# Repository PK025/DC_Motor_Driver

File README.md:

# DC_Motor_Driver

Bidirectional DC motor driver, compatible with Arduino.

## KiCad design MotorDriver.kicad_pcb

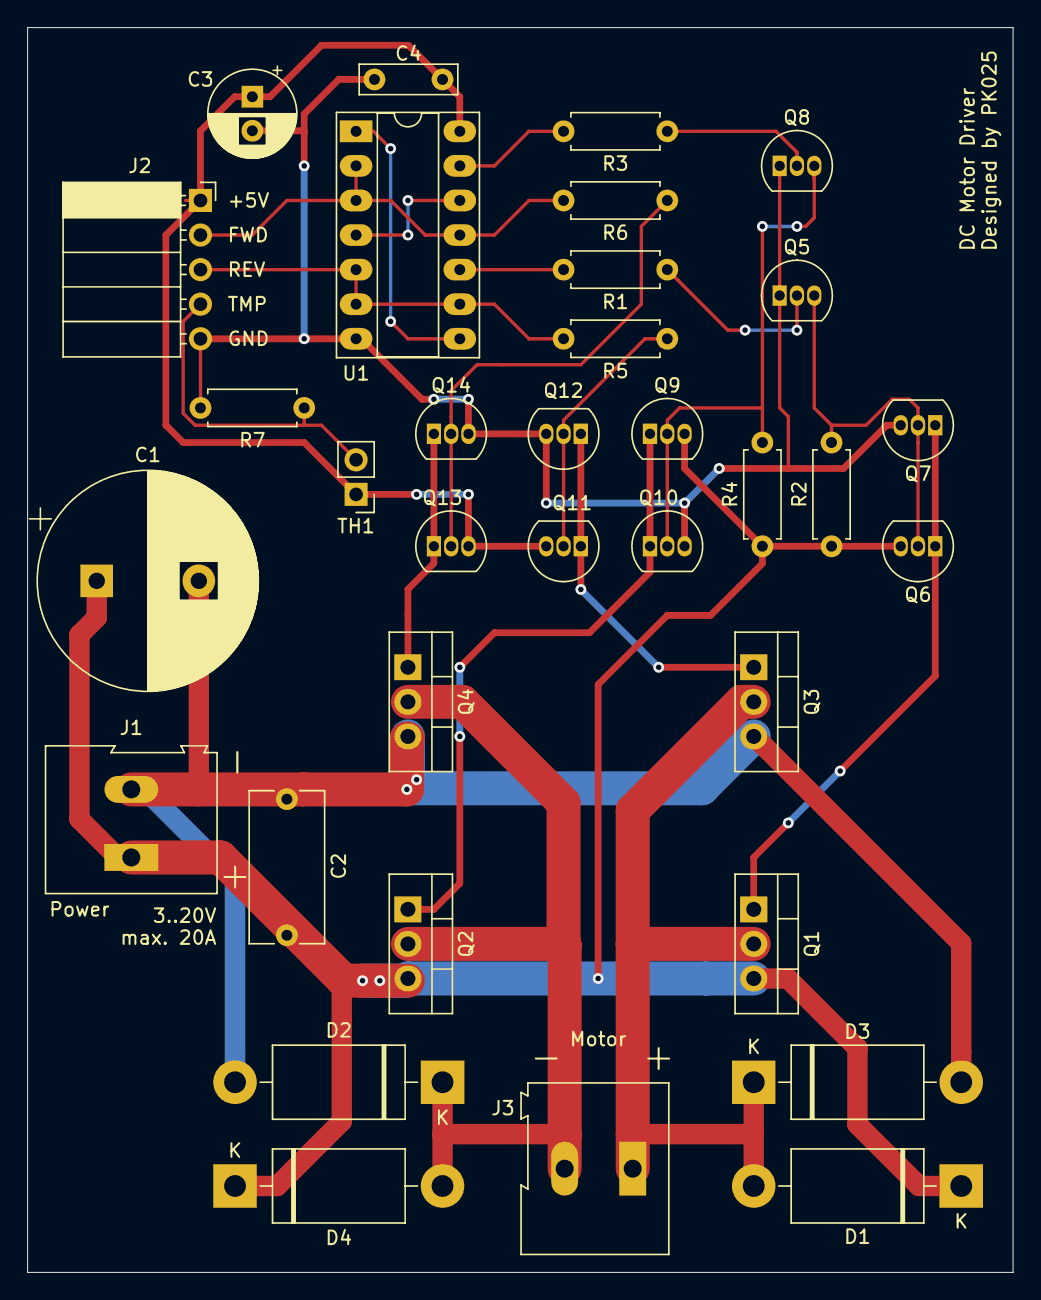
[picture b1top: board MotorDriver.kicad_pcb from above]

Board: 2 copper layers, 72.4 x 91.4 mm, 34 parts (0 on the bottom side), 23 nets.

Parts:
C1: 1000μF; CP_Radial_D16.0mm_P7.50mm
C2: 100nF; C_Rect_L11.0mm_W5.3mm_P10.00mm_MKT
C3: 47μF; CP_Radial_D6.3mm_P2.50mm
C4: 100nF; C_Rect_L7.0mm_W2.0mm_P5.00mm
D1, D2, D3, D4: 1N5822; D_DO-201AD_P15.24mm_Horizontal
J1: PowerIn; TerminalBlock_Altech_AK300-2_P5.00mm
J2: Arduino; PinSocket_1x05_P2.54mm_Horizontal
J3: Motor; TerminalBlock_Altech_AK300-2_P5.00mm
Q1, Q2: IRF4905; TO-220-3_Vertical
Q3, Q4: IRF3205; TO-220-3_Vertical
Q5, Q6, Q8, Q9, Q11, Q13: S8050; TO-92_Inline
Q7, Q10, Q12, Q14: S8550; TO-92_Inline
R1, R3, R5, R6, R7: 10k; R_Axial_DIN0207_L6.3mm_D2.5mm_P7.62mm_Horizontal
R2, R4: 3.3k; R_Axial_DIN0207_L6.3mm_D2.5mm_P7.62mm_Horizontal
TH1: 100k; PinHeader_1x02_P2.54mm_Vertical
U1: 74LS02; DIP-14_W7.62mm_Socket_LongPads

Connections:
+5V: C3.1, C4.1, J2.1, Q11.3, Q13.3, TH1.1, U1.14
+BATT: C1.1, C2.1, D1.1, D2.1, J1.1, Q1.3, Q2.3, Q6.3, Q9.3, R2.1, R4.1
-BATT: C1.2, C2.2, D3.2, D4.2, J1.2, Q3.3, Q4.3
/Q1G: Q1.1, Q6.1, Q7.1
/Q2G: Q2.1, Q9.1, Q10.1
/Q3G: Q3.1, Q11.1, Q12.1
/Q4G: Q4.1, Q13.1, Q14.1
FWD: J2.2, R6.2, U1.2, U1.3, U1.11
GND: C3.2, C4.2, J2.5, Q5.1, Q7.3, Q8.1, Q10.3, Q12.3, Q14.3, R7.2, U1.7
M+: D1.2, D3.1, J3.1, Q1.2, Q3.2
M-: D2.2, D4.1, J3.2, Q2.2, Q4.2
unnamed: Q5.2, R1.1
unnamed: Q5.3, Q6.2, Q7.2, R2.2
unnamed: Q8.2, R3.1
unnamed: Q8.3, Q9.2, Q10.2, R4.2
unnamed: Q11.2, Q12.2, R5.1
unnamed: Q13.2, Q14.2, R6.1
unnamed: R1.2, U1.10
unnamed: R3.2, U1.13
unnamed: U1.1, U1.8
unnamed: U1.4, U1.12
REV: J2.3, R5.2, U1.5, U1.6, U1.9
TMP: J2.4, R7.1, TH1.2
